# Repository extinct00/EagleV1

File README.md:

# EagleV1

## Low-cost split column-staggered ergonomic keyboard
A Corne-like split keyboard with a little bit wider thumb-cluster and more agressive pinky stagger. This keyboard is designed to be compatible with RedDragon LowProfile switches that are widely avaialable on AliExpress for very cheap. They have the same height as
Khail LP switches (around 12mm) and can be used with classic MX style keycaps, although some might hit the upper housing. Preffered are any keycaps compatible with Numphy keyboards or any 3D printed, either FDM or SLA.

---

## Table of Contents
1. [Introduction](#introduction)
2. [Features](#features)
3. [Bill of Materials](#bill-of-materials)
4. [Build Instructions](#build-instructions)
5. [Pictures](#pictures)
6. [Contributing](#contributing)
7. [License](#license)

---

## Introduction
This project is designed to create a split ergonomic keyboard that is both low-cost and low-profile. The keyboard is split into two halves, allowing for a more natural hand position and reducing strain during long typing sessions. The low-profile design ensures a sleek and modern look while maintaining comfort.

---

## Features
- **Split Design**: Ergonomically designed to reduce strain on your hands and wrists.
- **Low-Cost**: Built with affordable components to keep the project accessible.
- **Low-Profile**: Sleek and compact design for a modern look.
- **Customizable**: Open-source firmware and hardware for easy customization.

---

## Bill of Materials
Here’s a list of components you’ll need to build this keyboard. (You can fill this section with the specific parts you used.)

1. **Microcontroller**: (e.g., Pro Micro, RP2040, etc.)
2. **Key Switches**: (e.g., Low-profile mechanical switches)
3. **Keycaps**: (e.g., Low-profile keycaps)
4. **PCB or Handwiring Materials**: (e.g., PCB, diodes, wires)
5. **Case**: (e.g., 3D-printed or acrylic case)
6. **Connectors**: (e.g., TRRS cable for split communication)
7. **Miscellaneous**: (e.g., screws, standoffs, etc.)

---

## Build Instructions
Below is a step-by-step guide to building your split ergonomic keyboard. (You can fill in the details as you progress.)

### Step 1: Gather All Components
Ensure you have all the components listed in the [Bill of Materials](#bill-of-materials) section.

### Step 2: Prepare the PCB or Handwiring
- If using a PCB, solder the diodes and microcontroller.
- If handwiring, follow the wiring diagram and connect the switches to the microcontroller.

### Step 3: Assemble the Case
- Attach the switches to the case.
- Secure the PCB or handwired assembly into the case.

### Step 4: Connect the Two Halves
- Use a TRRS cable to connect the two halves of the keyboard.
- Ensure the firmware supports split communication.

### Step 5: Flash the Firmware
- Download and flash the firmware to the microcontroller.
- Customize the keymap if needed.

### Step 6: Test the Keyboard
- Connect the keyboard to your computer and test all keys.
- Make adjustments as necessary.

---

## Pictures
Here are some pictures of my progress and the final build. (You can add images from the `Pictures` folder as you go.)

---

## Contributing
Contributions are welcome! If you have any suggestions, improvements, or bug fixes, feel free to open an issue or submit a pull request.

---

## License
This project is licensed under the [MIT License](LICENSE). Feel free to use, modify, and distribute it as you see fit.

---

Happy building! 🎛️

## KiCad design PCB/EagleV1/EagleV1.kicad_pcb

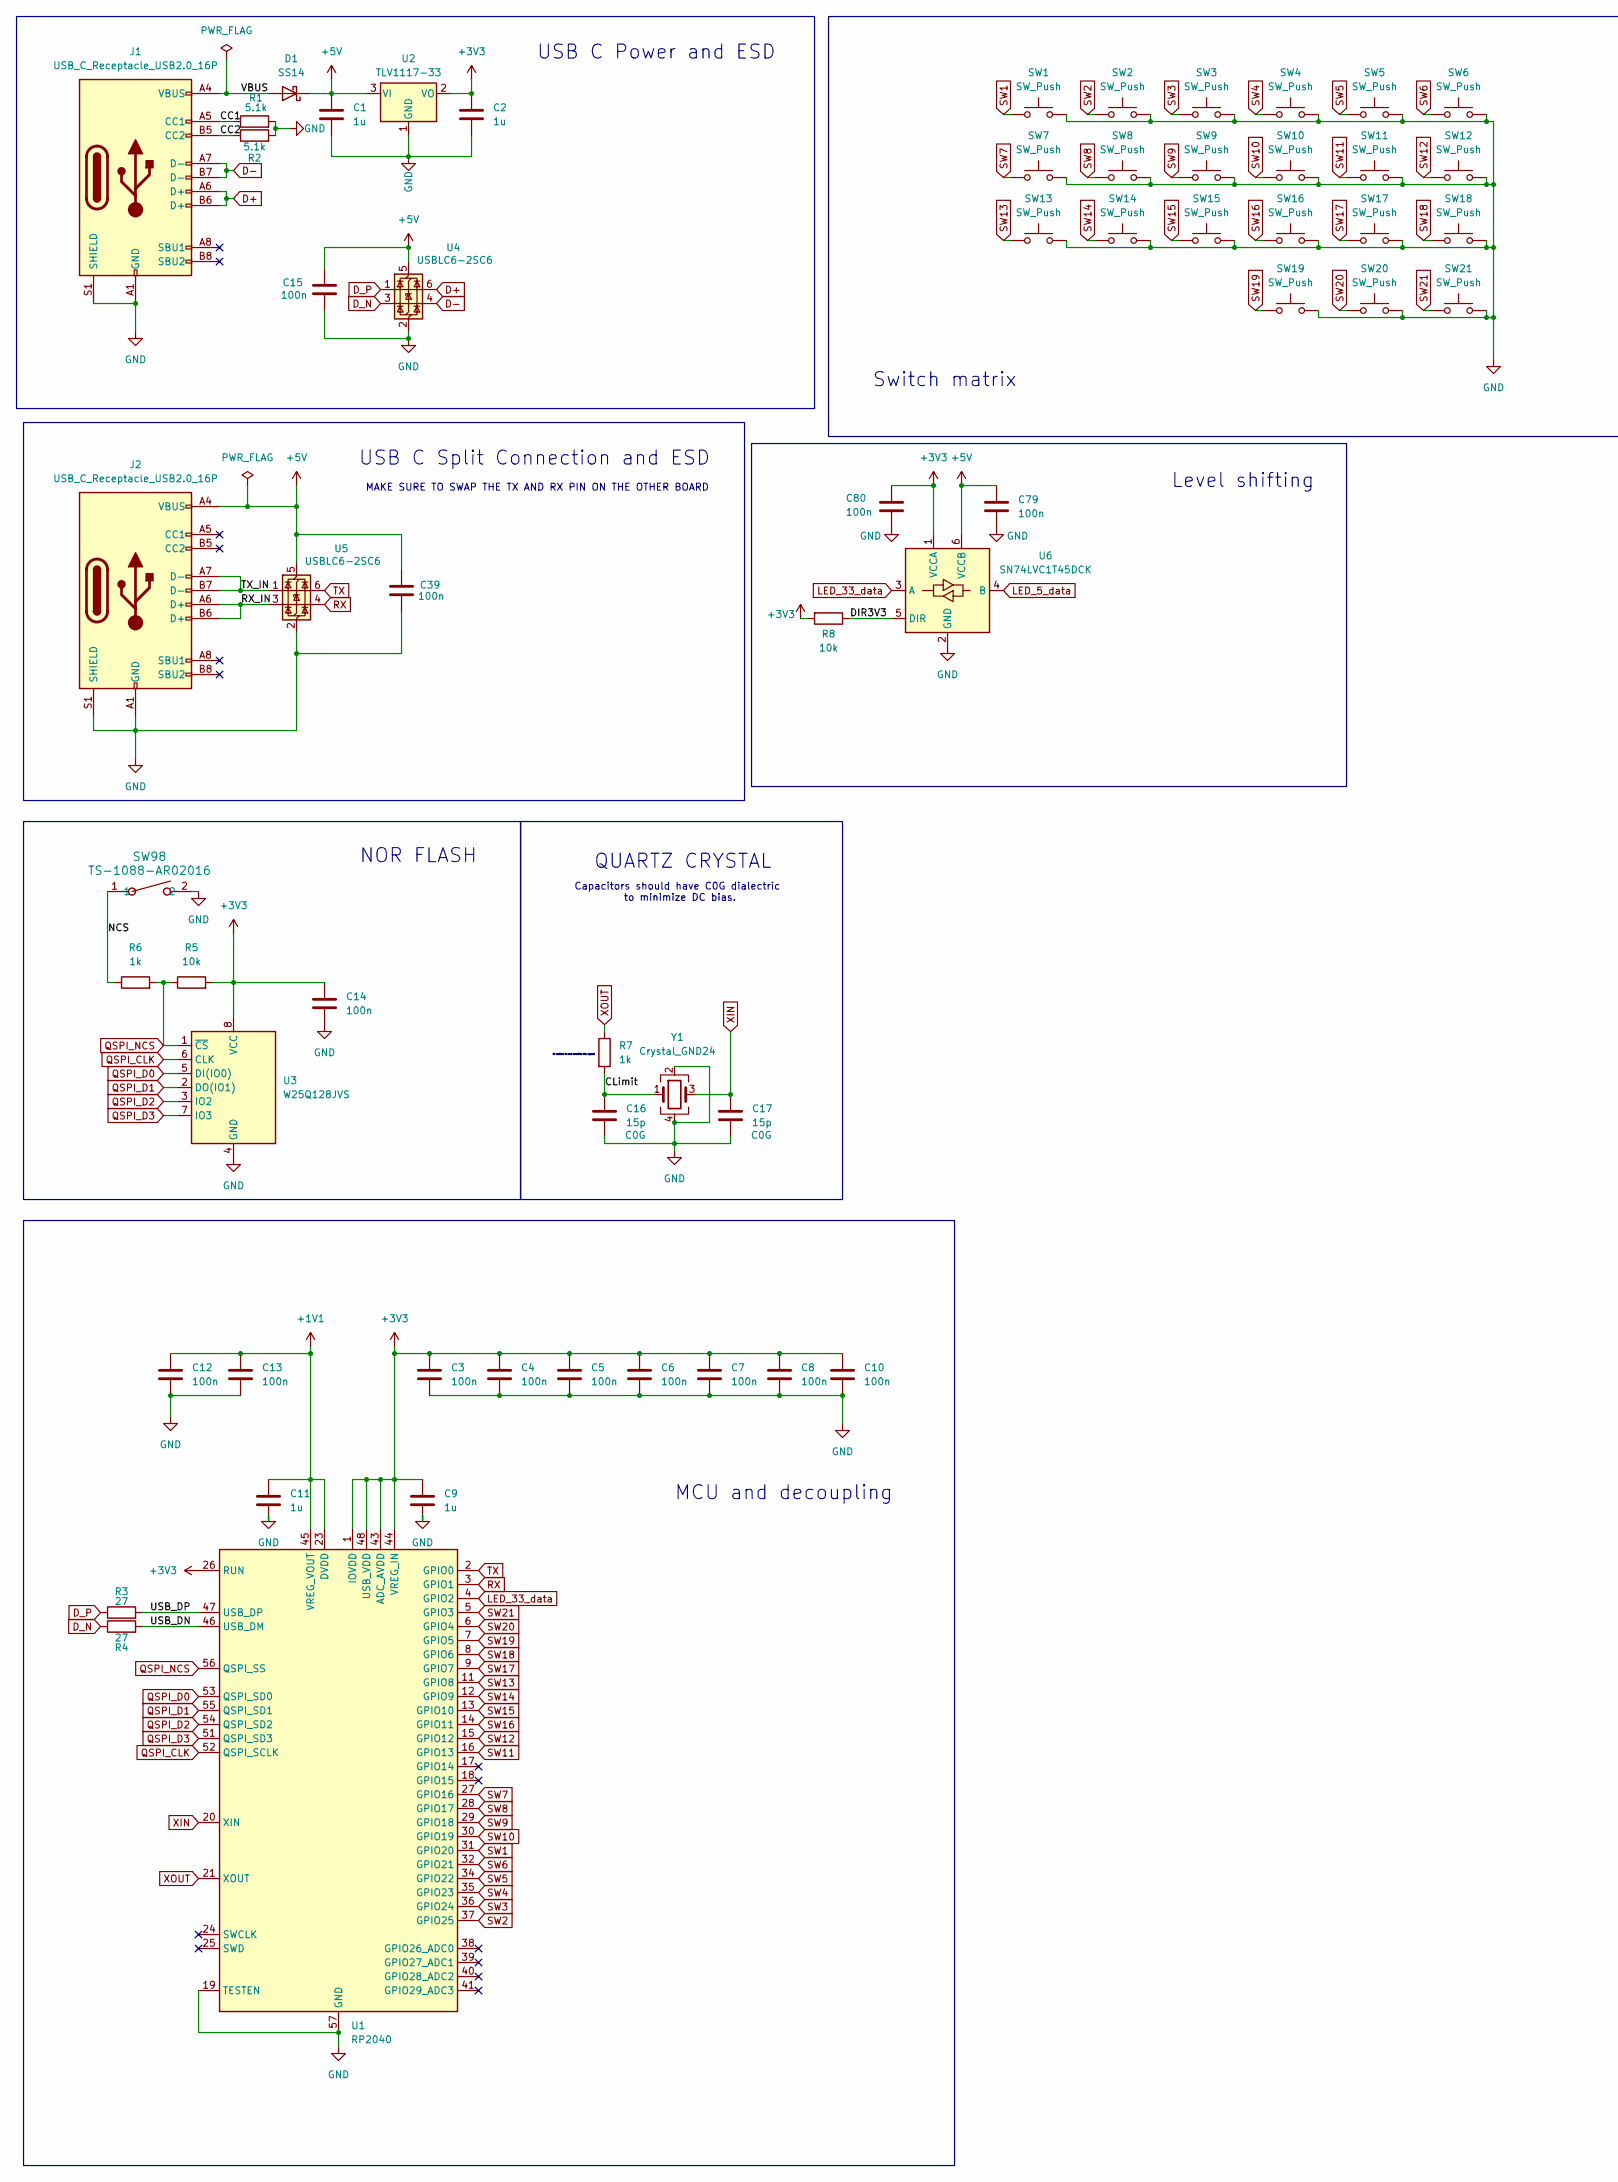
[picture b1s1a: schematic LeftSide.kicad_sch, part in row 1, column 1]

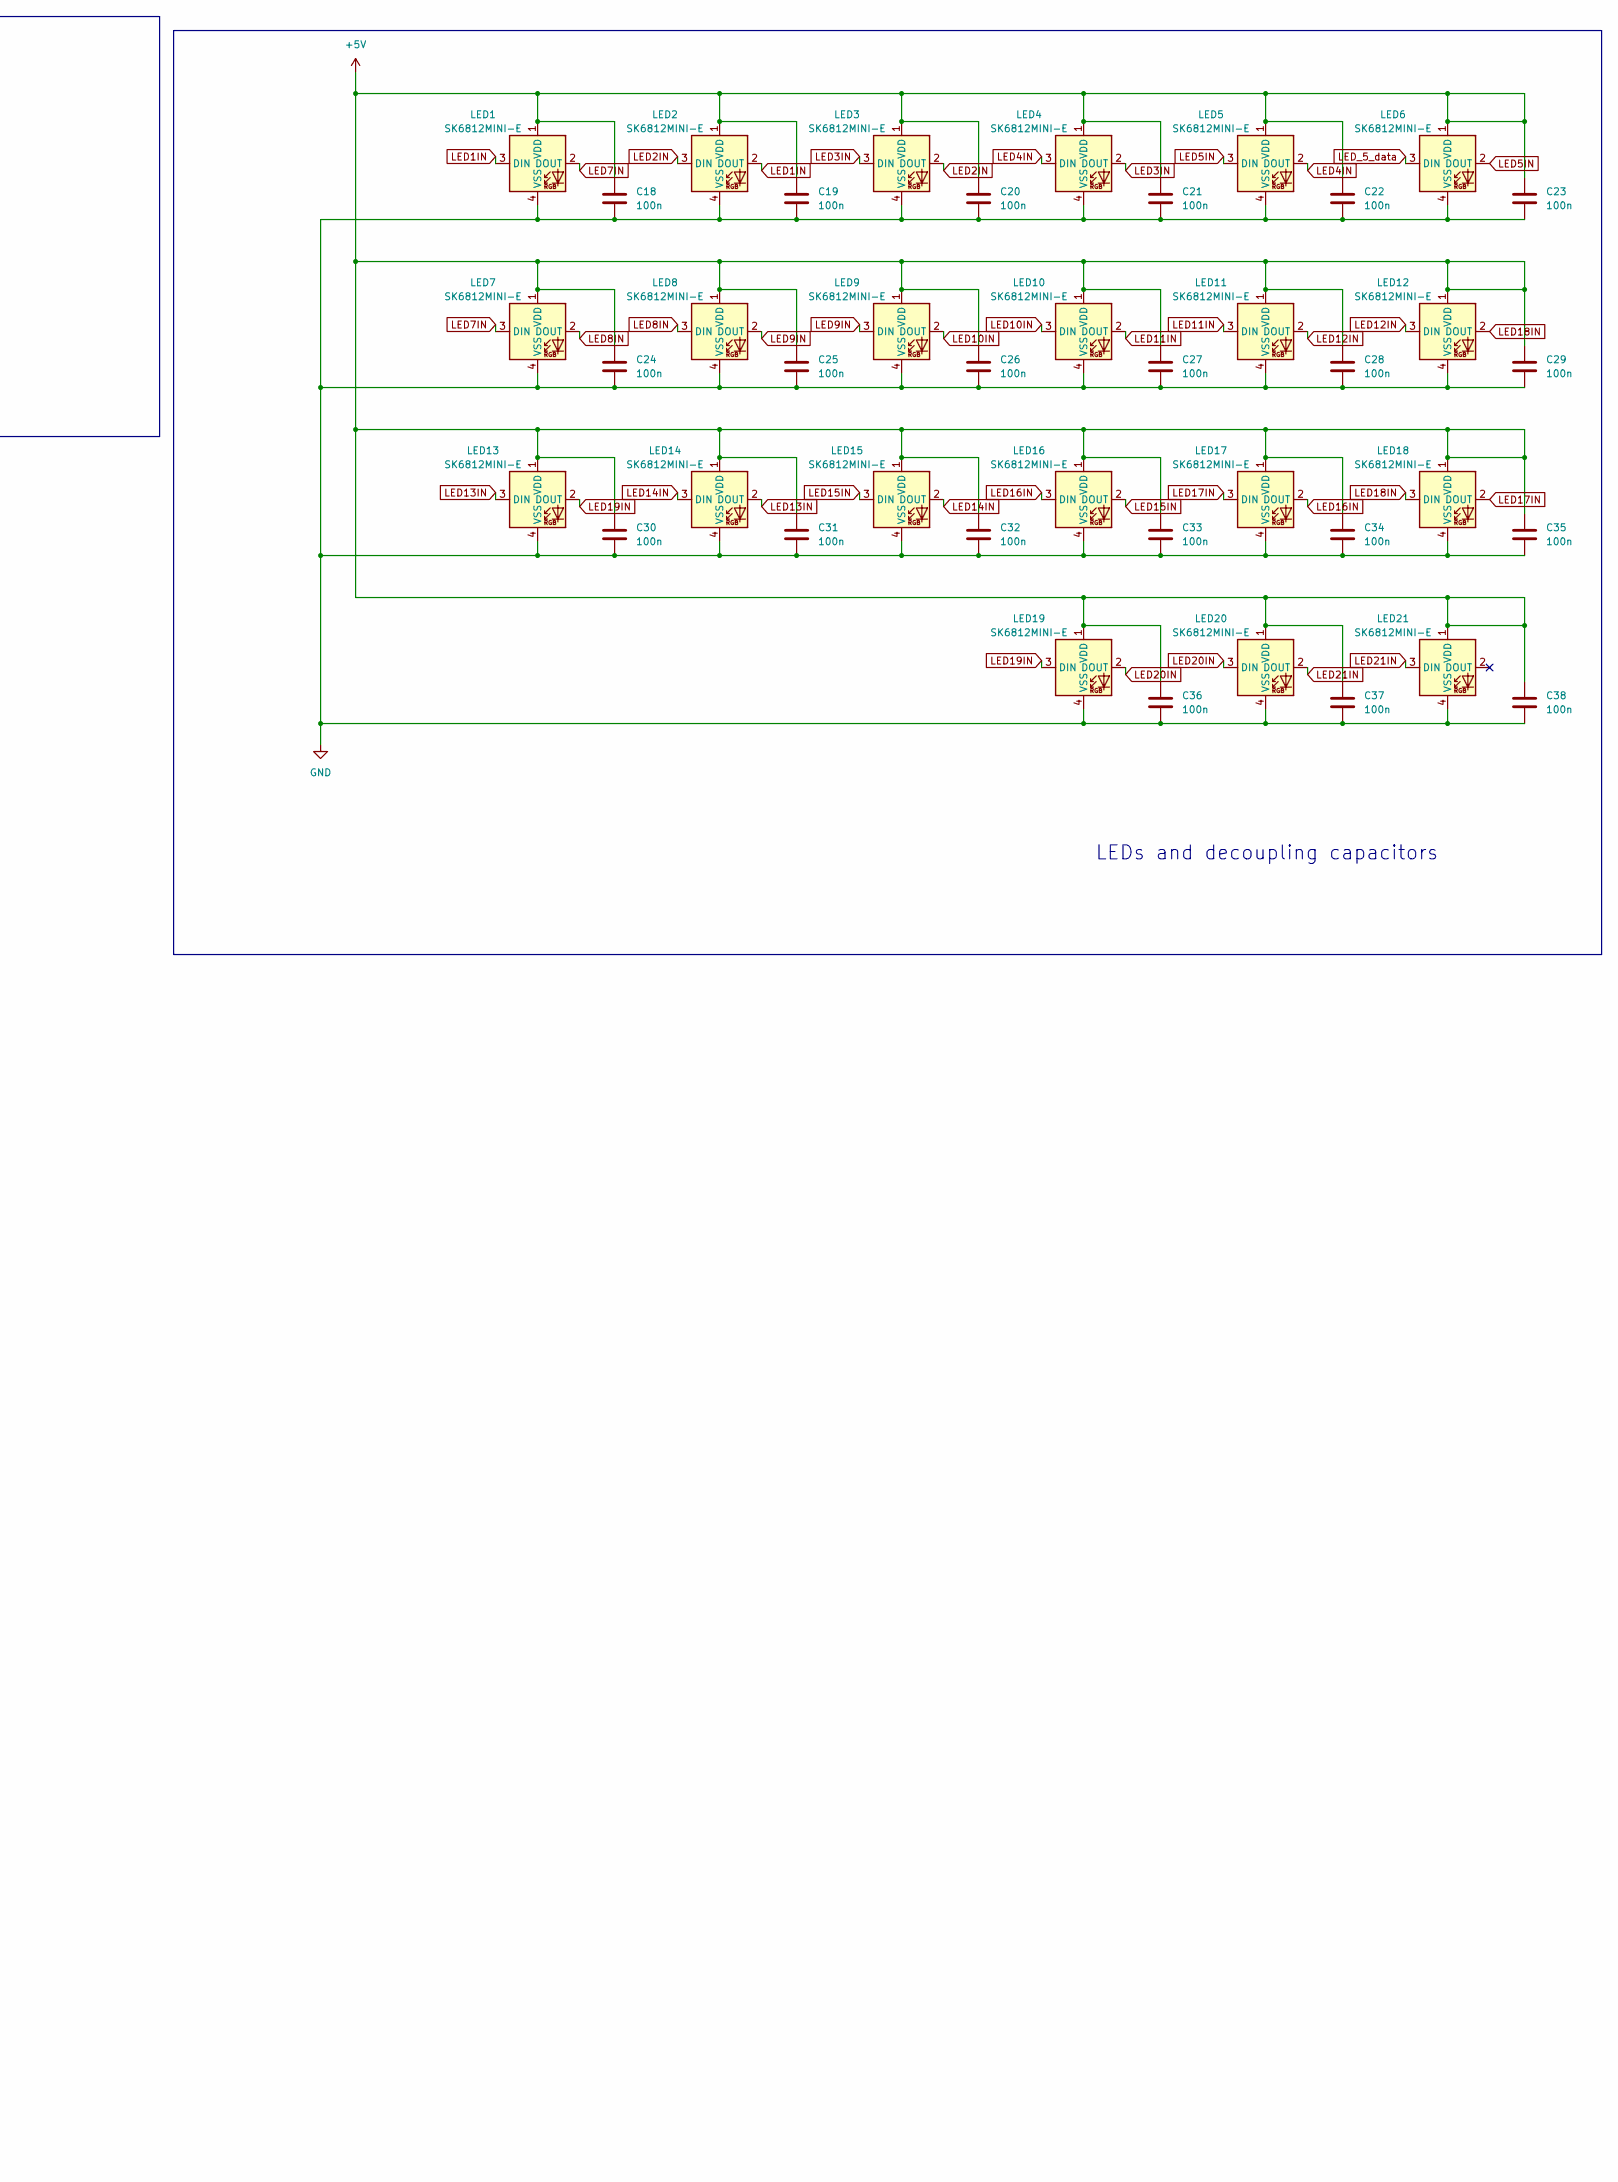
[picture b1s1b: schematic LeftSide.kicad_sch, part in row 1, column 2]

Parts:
C1, C2, C9, C11: 1u; C_0603_1608Metric
C3, C4, C5, C6, C7, C8, C10, C12, C13, C14, C15, C18, C19, C20, C21, C22, C23, C24, C25, C26, C27, C28, C29, C30, C31, C32, C33, C34, C35, C36, C37, C38, C39, C79, C80: 100n; C_0402_1005Metric
C16, C17: 15p; C_0402_1005Metric
D1: SS14; D_SMA
J1, J2: USB_C_Receptacle_USB2.0_16P; USB_C_Receptacle_G-Switch_GT-USB-7010ASV
LED1, LED2, LED3, LED4, LED5, LED6, LED7, LED8, LED9, LED10, LED11, LED12, LED13, LED14, LED15, LED16, LED17, LED18, LED19, LED20, LED21: SK6812MINI-E; LED_6028R
R1, R2: 5.1k; R_0402_1005Metric
R3, R4: 27; R_0402_1005Metric
R5, R8: 10k; R_0402_1005Metric
R6, R7: 1k; R_0402_1005Metric
SW1, SW2, SW3, SW4, SW5, SW6, SW7, SW8, SW9, SW10, SW11, SW12, SW13, SW14, SW15, SW16, SW17, SW18, SW19, SW20, SW21: SW_Push; SW_Redragon_LowProfile_PCB_1.00u
SW98: TS-1088-AR02016; SW_TS-1088_XNP
U1: RP2040; QFN-56-1EP_7x7mm_P0.4mm_EP3.2x3.2mm
U2: TLV1117-33; SOT-223-3_TabPin2
U3: W25Q128JVS; SOIC-8_5.23x5.23mm_P1.27mm
U4, U5: USBLC6-2SC6; SOT-23-6
U6: SN74LVC1T45DCK; SOT-363_SC-70-6
Y1: Crystal_GND24; Crystal_SMD_3225-4Pin_3.2x2.5mm

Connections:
+1V1: C11.1, C12.1, C13.1, U1.23 (DVDD), U1.45 (VREG_VOUT), U1.50 (DVDD)
+3V3: C2.1, C3.1, C4.1, C5.1, C6.1, C7.1, C8.1, C9.1, C10.1, C14.1, C80.1, R5.2, R8.2, U1.1 (IOVDD), U1.10 (IOVDD), U1.22 (IOVDD), U1.26 (RUN), U1.33 (IOVDD), U1.42 (IOVDD), U1.43 (ADC_AVDD), U1.44 (VREG_IN), U1.48 (USB_VDD), U1.49 (IOVDD), U2.2 (VO), U3.8 (VCC), U6.1 (VCCA)
+5V: C1.1, C15.2, C18.2, C19.2, C20.2, C21.2, C22.2, C23.2, C24.2, C25.2, C26.2, C27.2, C28.2, C29.2, C30.2, C31.2, C32.2, C33.2, C34.2, C35.2, C36.2, C37.2, C38.2, C39.2, C79.1, D1.1 (K), J2.A4 (VBUS), J2.A9 (VBUS), J2.B4 (VBUS), J2.B9 (VBUS), LED1.1 (VDD), LED2.1 (VDD), LED3.1 (VDD), LED4.1 (VDD), LED5.1 (VDD), LED6.1 (VDD), LED7.1 (VDD), LED8.1 (VDD), LED9.1 (VDD), LED10.1 (VDD), LED11.1 (VDD), LED12.1 (VDD), LED13.1 (VDD), LED14.1 (VDD), LED15.1 (VDD), LED16.1 (VDD), LED17.1 (VDD), LED18.1 (VDD), LED19.1 (VDD), LED20.1 (VDD), LED21.1 (VDD), U2.3 (VI), U4.5 (VBUS), U5.5 (VBUS), U6.6 (VCCB)
/LeftSide/CC1: J1.A5 (CC1), R1.1
/LeftSide/CC2: J1.B5 (CC2), R2.1
/LeftSide/CLimit: C16.1, R7.2, Y1.1
/LeftSide/DIR3V3: R8.1, U6.5 (DIR)
/LeftSide/NCS: R6.1, SW98.1
/LeftSide/RX_IN: J2.A6 (D+), J2.B6 (D+), U5.3 (I/O2)
/LeftSide/TX_IN: J2.A7 (D-), J2.B7 (D-), U5.1 (I/O1)
/LeftSide/USB_DN: R4.2, U1.46 (USB_DM)
/LeftSide/USB_DP: R3.2, U1.47 (USB_DP)
/LeftSide/VBUS: D1.2 (A), J1.A4 (VBUS), J1.A9 (VBUS), J1.B4 (VBUS), J1.B9 (VBUS)
D+: J1.A6 (D+), J1.B6 (D+), U4.6 (I/O1)
D-: J1.A7 (D-), J1.B7 (D-), U4.4 (I/O2)
D_N: R4.1, U4.3 (I/O2)
D_P: R3.1, U4.1 (I/O1)
GND: C1.2, C2.2, C3.2, C4.2, C5.2, C6.2, C7.2, C8.2, C9.2, C10.2, C11.2, C12.2, C13.2, C14.2, C15.1, C16.2, C17.2, C18.1, C19.1, C20.1, C21.1, C22.1, C23.1, C24.1, C25.1, C26.1, C27.1, C28.1, C29.1, C30.1, C31.1, C32.1, C33.1, C34.1, C35.1, C36.1, C37.1, C38.1, C39.1, C79.2, C80.2, J1.A1 (GND), J1.A12 (GND), J1.B1 (GND), J1.B12 (GND), J1.S1 (SHIELD), J2.A1 (GND), J2.A12 (GND), J2.B1 (GND), J2.B12 (GND), J2.S1 (SHIELD), LED1.4 (VSS), LED2.4 (VSS), LED3.4 (VSS), LED4.4 (VSS), LED5.4 (VSS), LED6.4 (VSS), LED7.4 (VSS), LED8.4 (VSS), LED9.4 (VSS), LED10.4 (VSS), LED11.4 (VSS), LED12.4 (VSS), LED13.4 (VSS), LED14.4 (VSS), LED15.4 (VSS), LED16.4 (VSS), LED17.4 (VSS), LED18.4 (VSS), LED19.4 (VSS), LED20.4 (VSS), LED21.4 (VSS), R1.2, R2.2, SW1.2, SW2.2, SW3.2, SW4.2, SW5.2, SW6.2, SW7.2, SW8.2, SW9.2, SW10.2, SW11.2, SW12.2, SW13.2, SW14.2, SW15.2, SW16.2, SW17.2, SW18.2, SW19.2, SW20.2, SW21.2, SW98.2, U1.19 (TESTEN), U1.57 (GND), U2.1 (GND), U3.4 (GND), U4.2 (GND), U5.2 (GND), U6.2 (GND), Y1.2, Y1.4
LED1IN: LED1.3 (DIN), LED2.2 (DOUT)
LED2IN: LED2.3 (DIN), LED3.2 (DOUT)
LED3IN: LED3.3 (DIN), LED4.2 (DOUT)
LED4IN: LED4.3 (DIN), LED5.2 (DOUT)
LED5IN: LED5.3 (DIN), LED6.2 (DOUT)
LED7IN: LED1.2 (DOUT), LED7.3 (DIN)
LED8IN: LED7.2 (DOUT), LED8.3 (DIN)
LED9IN: LED8.2 (DOUT), LED9.3 (DIN)
LED10IN: LED9.2 (DOUT), LED10.3 (DIN)
LED11IN: LED10.2 (DOUT), LED11.3 (DIN)
LED12IN: LED11.2 (DOUT), LED12.3 (DIN)
LED13IN: LED13.3 (DIN), LED14.2 (DOUT)
LED14IN: LED14.3 (DIN), LED15.2 (DOUT)
LED15IN: LED15.3 (DIN), LED16.2 (DOUT)
LED16IN: LED16.3 (DIN), LED17.2 (DOUT)
LED17IN: LED17.3 (DIN), LED18.2 (DOUT)
LED18IN: LED12.2 (DOUT), LED18.3 (DIN)
LED19IN: LED13.2 (DOUT), LED19.3 (DIN)
LED20IN: LED19.2 (DOUT), LED20.3 (DIN)
LED21IN: LED20.2 (DOUT), LED21.3 (DIN)
LED_5_data: LED6.3 (DIN), U6.4 (B)
LED_33_data: U1.4 (GPIO2), U6.3 (A)
QSPI_CLK: U1.52 (QSPI_SCLK), U3.6 (CLK)
QSPI_D0: U1.53 (QSPI_SD0), U3.5 (DI(IO0))
QSPI_D1: U1.55 (QSPI_SD1), U3.2 (DO(IO1))
QSPI_D2: U1.54 (QSPI_SD2), U3.3 (IO2)
QSPI_D3: U1.51 (QSPI_SD3), U3.7 (IO3)
QSPI_NCS: R5.1, R6.2, U1.56 (QSPI_SS), U3.1 (~CS)
RX: U1.3 (GPIO1), U5.4 (I/O2)
SW1: SW1.1, U1.31 (GPIO20)
SW2: SW2.1, U1.37 (GPIO25)
SW3: SW3.1, U1.36 (GPIO24)
SW4: SW4.1, U1.35 (GPIO23)
SW5: SW5.1, U1.34 (GPIO22)
SW6: SW6.1, U1.32 (GPIO21)
SW7: SW7.1, U1.27 (GPIO16)
SW8: SW8.1, U1.28 (GPIO17)
SW9: SW9.1, U1.29 (GPIO18)
SW10: SW10.1, U1.30 (GPIO19)
SW11: SW11.1, U1.16 (GPIO13)
SW12: SW12.1, U1.15 (GPIO12)
SW13: SW13.1, U1.11 (GPIO8)
SW14: SW14.1, U1.12 (GPIO9)
SW15: SW15.1, U1.13 (GPIO10)
SW16: SW16.1, U1.14 (GPIO11)
SW17: SW17.1, U1.9 (GPIO7)
SW18: SW18.1, U1.8 (GPIO6)
SW19: SW19.1, U1.7 (GPIO5)
SW20: SW20.1, U1.6 (GPIO4)
SW21: SW21.1, U1.5 (GPIO3)
TX: U1.2 (GPIO0), U5.6 (I/O1)
XIN: C17.1, U1.20 (XIN), Y1.3
XOUT: R7.1, U1.21 (XOUT)

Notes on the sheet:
Capacitors should have C0G dialectric to minimize DC bias.
NOR FLASH
MAKE SURE TO SWAP THE TX AND RX PIN ON THE OTHER BOARD
USB C Power and ESD
LEDs and decoupling capacitors
1k resistor to not overdrive the crystal
USB C Split Connection and ESD
Level shifting
MCU and decoupling
QUARTZ CRYSTAL
Switch matrix

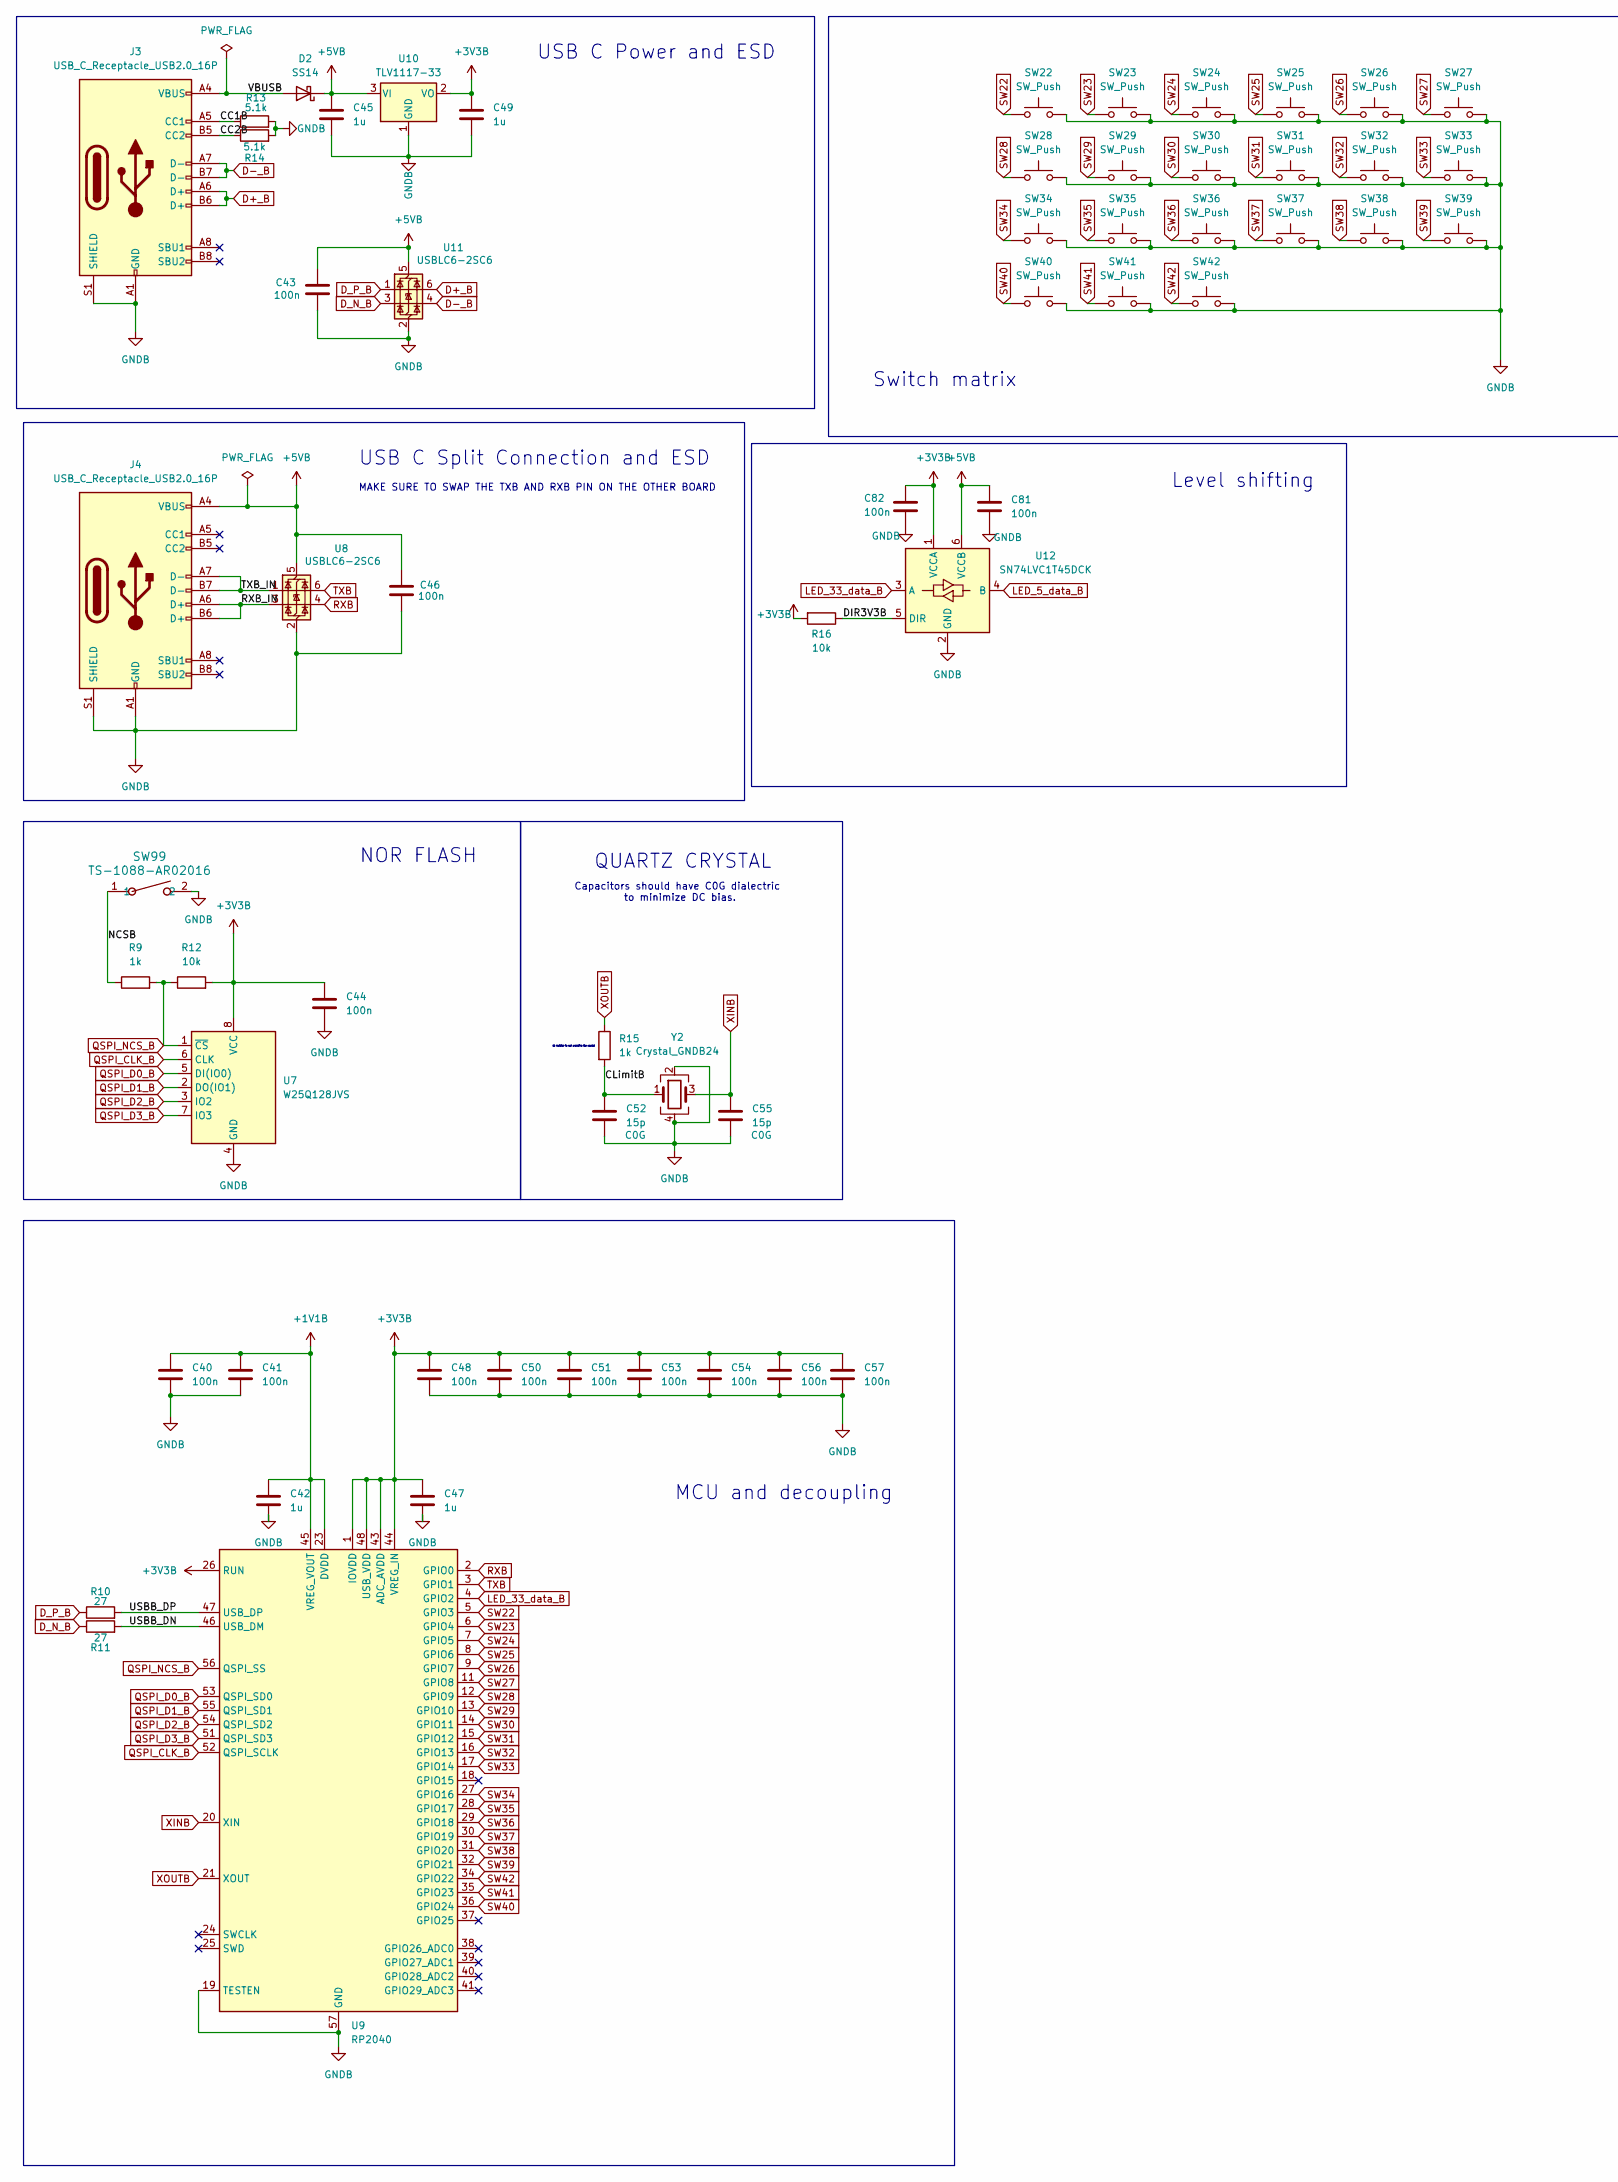
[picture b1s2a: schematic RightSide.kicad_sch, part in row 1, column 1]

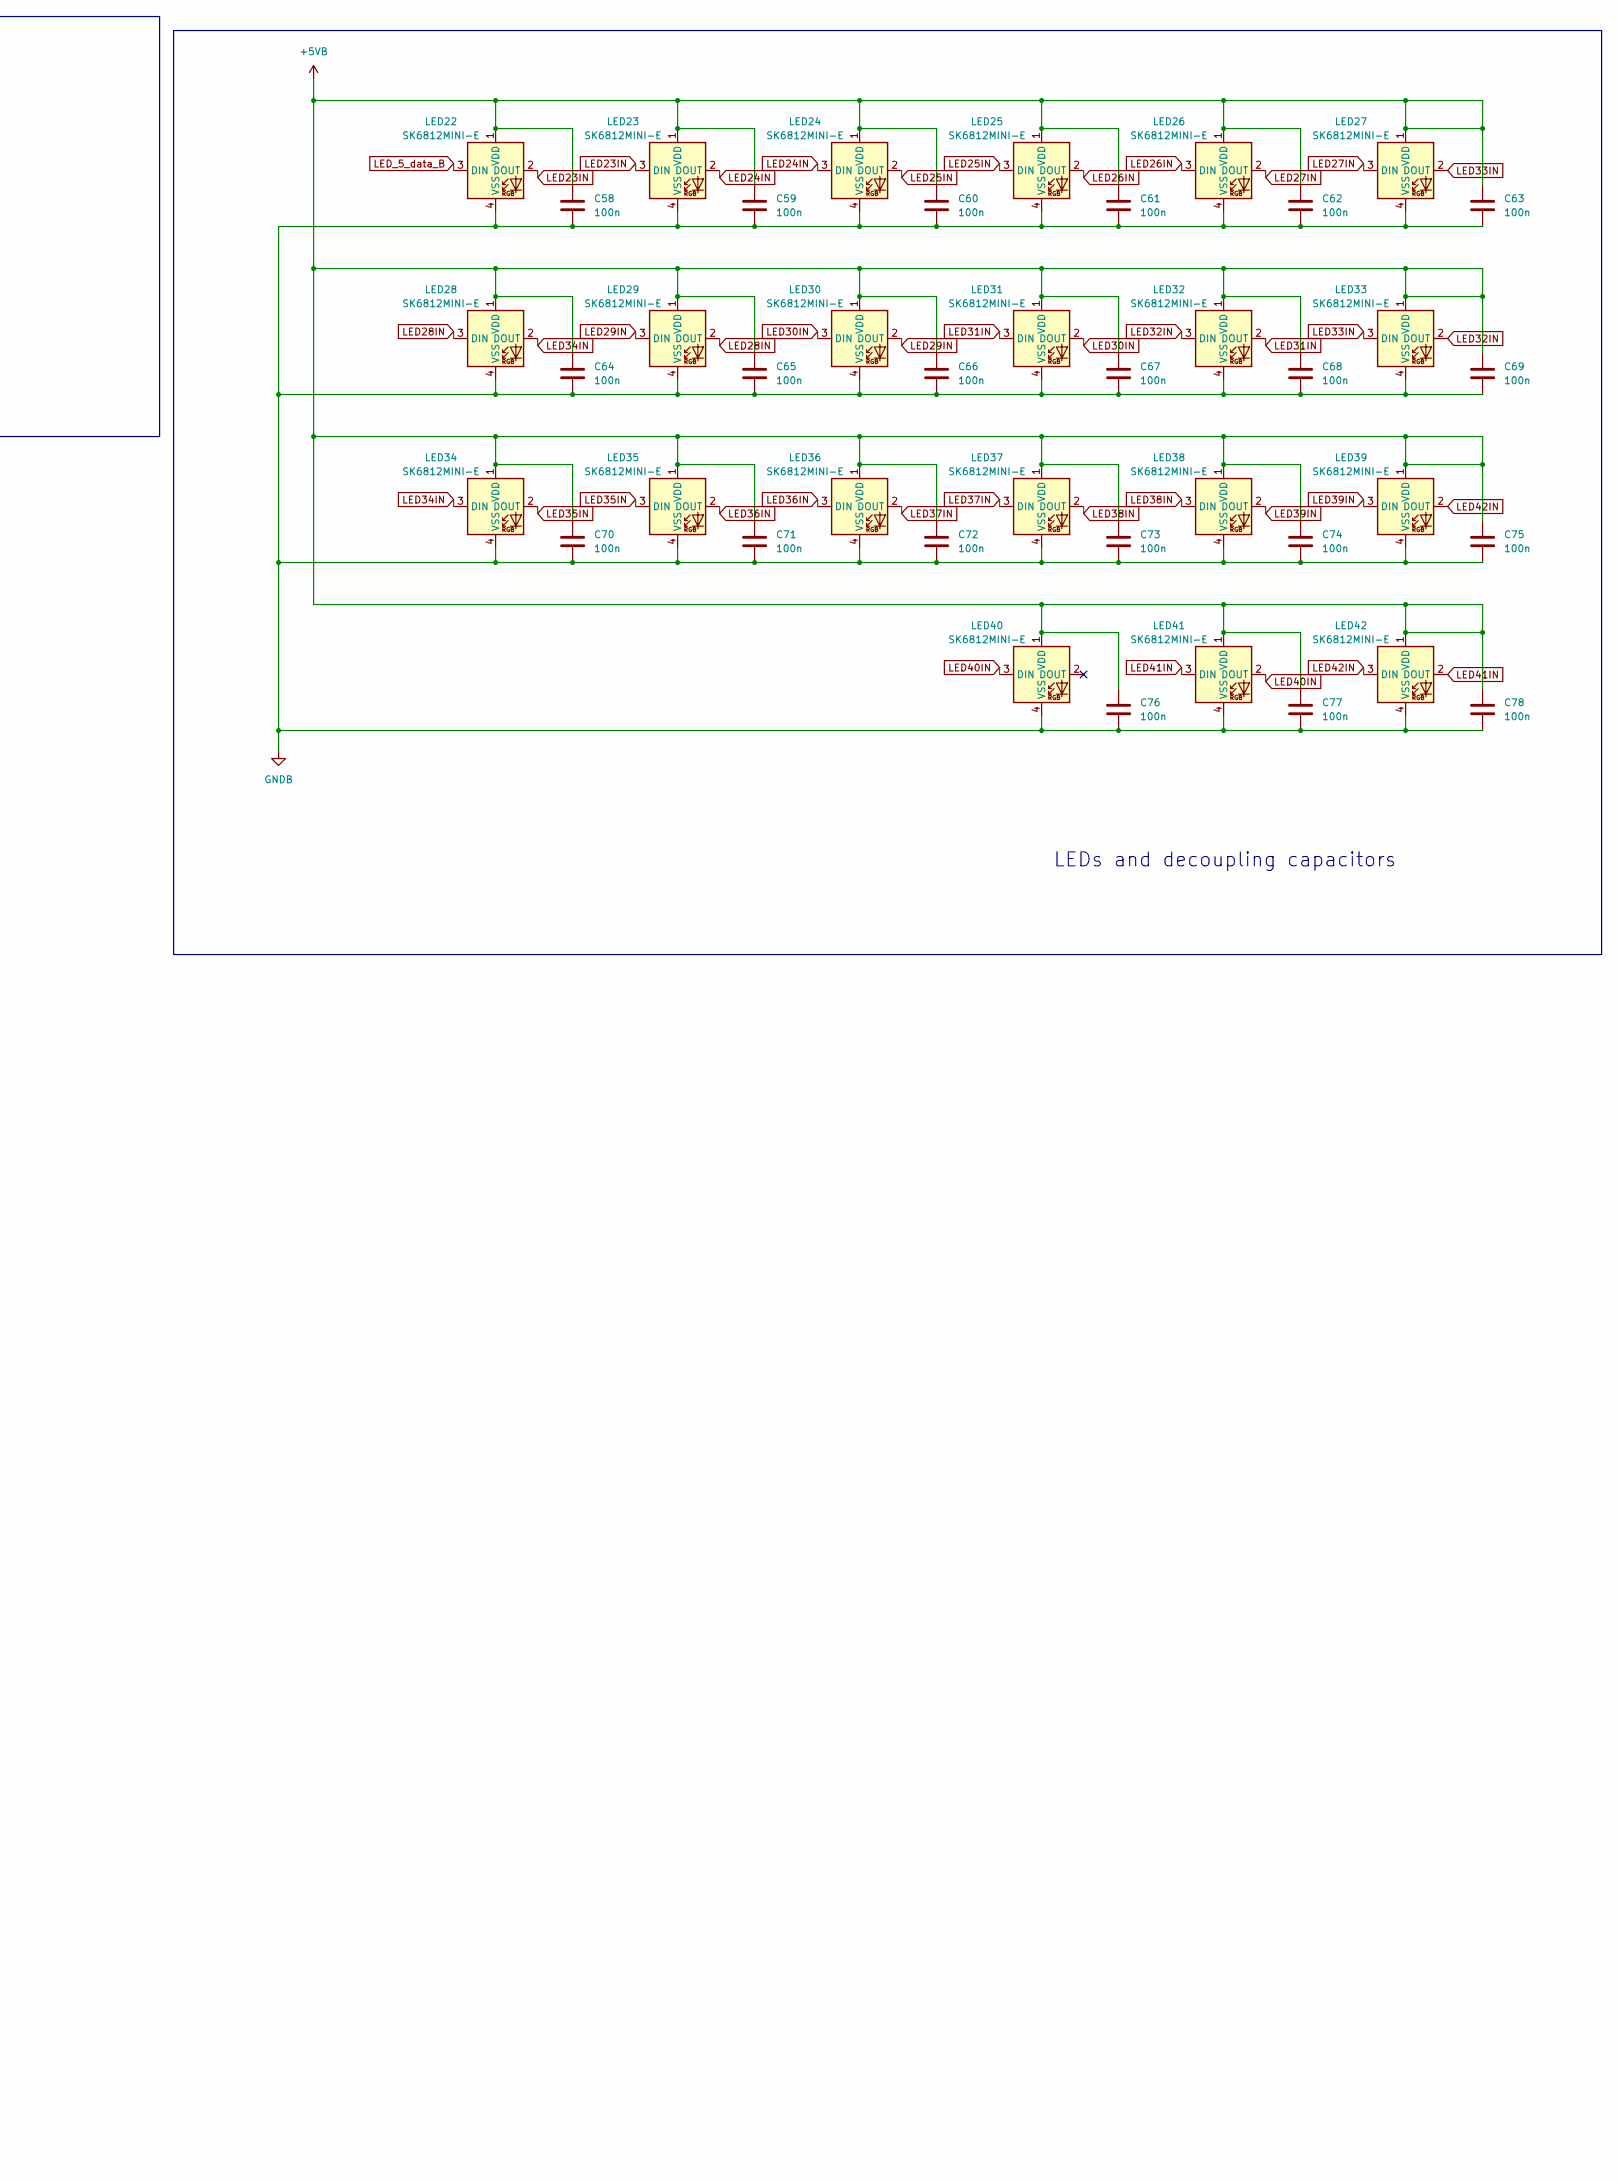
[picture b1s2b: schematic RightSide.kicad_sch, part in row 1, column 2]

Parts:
C40, C41, C43, C44, C46, C48, C50, C51, C53, C54, C56, C57, C58, C59, C60, C61, C62, C63, C64, C65, C66, C67, C68, C69, C70, C71, C72, C73, C74, C75, C76, C77, C78, C81, C82: 100n; C_0402_1005Metric
C42, C45, C47, C49: 1u; C_0603_1608Metric
C52, C55: 15p; C_0402_1005Metric
D2: SS14; D_SMA
J3, J4: USB_C_Receptacle_USB2.0_16P; USB_C_Receptacle_G-Switch_GT-USB-7010ASV
LED22, LED23, LED24, LED25, LED26, LED27, LED28, LED29, LED30, LED31, LED32, LED33, LED34, LED35, LED36, LED37, LED38, LED39, LED40, LED41, LED42: SK6812MINI-E; LED_6028R
R9, R15: 1k; R_0402_1005Metric
R10, R11: 27; R_0402_1005Metric
R12, R16: 10k; R_0402_1005Metric
R13, R14: 5.1k; R_0402_1005Metric
SW22, SW23, SW24, SW25, SW26, SW27, SW28, SW29, SW30, SW31, SW32, SW33, SW34, SW35, SW36, SW37, SW38, SW39, SW40, SW41, SW42: SW_Push; SW_Redragon_LowProfile_PCB_1.00u
SW99: TS-1088-AR02016; SW_TS-1088_XNP
U7: W25Q128JVS; SOIC-8_5.23x5.23mm_P1.27mm
U8, U11: USBLC6-2SC6; SOT-23-6
U9: RP2040; QFN-56-1EP_7x7mm_P0.4mm_EP3.2x3.2mm
U10: TLV1117-33; SOT-223-3_TabPin2
U12: SN74LVC1T45DCK; SOT-363_SC-70-6
Y2: Crystal_GNDB24; Crystal_SMD_3225-4Pin_3.2x2.5mm

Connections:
+1V1B: C40.1, C41.1, C42.1, U9.23 (DVDD), U9.45 (VREG_VOUT), U9.50 (DVDD)
+3V3B: C44.1, C47.1, C48.1, C49.1, C50.1, C51.1, C53.1, C54.1, C56.1, C57.1, C82.1, R12.2, R16.2, U7.8 (VCC), U9.1 (IOVDD), U9.10 (IOVDD), U9.22 (IOVDD), U9.26 (RUN), U9.33 (IOVDD), U9.42 (IOVDD), U9.43 (ADC_AVDD), U9.44 (VREG_IN), U9.48 (USB_VDD), U9.49 (IOVDD), U10.2 (VO), U12.1 (VCCA)
+5VB: C43.2, C45.1, C46.2, C58.2, C59.2, C60.2, C61.2, C62.2, C63.2, C64.2, C65.2, C66.2, C67.2, C68.2, C69.2, C70.2, C71.2, C72.2, C73.2, C74.2, C75.2, C76.2, C77.2, C78.2, C81.1, D2.1 (K), J4.A4 (VBUS), J4.A9 (VBUS), J4.B4 (VBUS), J4.B9 (VBUS), LED22.1 (VDD), LED23.1 (VDD), LED24.1 (VDD), LED25.1 (VDD), LED26.1 (VDD), LED27.1 (VDD), LED28.1 (VDD), LED29.1 (VDD), LED30.1 (VDD), LED31.1 (VDD), LED32.1 (VDD), LED33.1 (VDD), LED34.1 (VDD), LED35.1 (VDD), LED36.1 (VDD), LED37.1 (VDD), LED38.1 (VDD), LED39.1 (VDD), LED40.1 (VDD), LED41.1 (VDD), LED42.1 (VDD), U8.5 (VBUS), U10.3 (VI), U11.5 (VBUS), U12.6 (VCCB)
/RightSide/CC1B: J3.A5 (CC1), R13.1
/RightSide/CC2B: J3.B5 (CC2), R14.1
/RightSide/CLimitB: C52.1, R15.2, Y2.1
/RightSide/DIR3V3B: R16.1, U12.5 (DIR)
/RightSide/NCSB: R9.1, SW99.1
/RightSide/RXB_IN: J4.A6 (D+), J4.B6 (D+), U8.3 (I/O2)
/RightSide/TXB_IN: J4.A7 (D-), J4.B7 (D-), U8.1 (I/O1)
/RightSide/USBB_DN: R11.2, U9.46 (USB_DM)
/RightSide/USBB_DP: R10.2, U9.47 (USB_DP)
/RightSide/VBUSB: D2.2 (A), J3.A4 (VBUS), J3.A9 (VBUS), J3.B4 (VBUS), J3.B9 (VBUS)
D+_B: J3.A6 (D+), J3.B6 (D+), U11.6 (I/O1)
D-_B: J3.A7 (D-), J3.B7 (D-), U11.4 (I/O2)
D_N_B: R11.1, U11.3 (I/O2)
D_P_B: R10.1, U11.1 (I/O1)
GNDB: C40.2, C41.2, C42.2, C43.1, C44.2, C45.2, C46.1, C47.2, C48.2, C49.2, C50.2, C51.2, C52.2, C53.2, C54.2, C55.2, C56.2, C57.2, C58.1, C59.1, C60.1, C61.1, C62.1, C63.1, C64.1, C65.1, C66.1, C67.1, C68.1, C69.1, C70.1, C71.1, C72.1, C73.1, C74.1, C75.1, C76.1, C77.1, C78.1, C81.2, C82.2, J3.A1 (GND), J3.A12 (GND), J3.B1 (GND), J3.B12 (GND), J3.S1 (SHIELD), J4.A1 (GND), J4.A12 (GND), J4.B1 (GND), J4.B12 (GND), J4.S1 (SHIELD), LED22.4 (VSS), LED23.4 (VSS), LED24.4 (VSS), LED25.4 (VSS), LED26.4 (VSS), LED27.4 (VSS), LED28.4 (VSS), LED29.4 (VSS), LED30.4 (VSS), LED31.4 (VSS), LED32.4 (VSS), LED33.4 (VSS), LED34.4 (VSS), LED35.4 (VSS), LED36.4 (VSS), LED37.4 (VSS), LED38.4 (VSS), LED39.4 (VSS), LED40.4 (VSS), LED41.4 (VSS), LED42.4 (VSS), R13.2, R14.2, SW22.2, SW23.2, SW24.2, SW25.2, SW26.2, SW27.2, SW28.2, SW29.2, SW30.2, SW31.2, SW32.2, SW33.2, SW34.2, SW35.2, SW36.2, SW37.2, SW38.2, SW39.2, SW40.2, SW41.2, SW42.2, SW99.2, U7.4 (GND), U8.2 (GND), U9.19 (TESTEN), U9.57 (GND), U10.1 (GND), U11.2 (GND), U12.2 (GND), Y2.2, Y2.4
LED23IN: LED22.2 (DOUT), LED23.3 (DIN)
LED24IN: LED23.2 (DOUT), LED24.3 (DIN)
LED25IN: LED24.2 (DOUT), LED25.3 (DIN)
LED26IN: LED25.2 (DOUT), LED26.3 (DIN)
LED27IN: LED26.2 (DOUT), LED27.3 (DIN)
LED28IN: LED28.3 (DIN), LED29.2 (DOUT)
LED29IN: LED29.3 (DIN), LED30.2 (DOUT)
LED30IN: LED30.3 (DIN), LED31.2 (DOUT)
LED31IN: LED31.3 (DIN), LED32.2 (DOUT)
LED32IN: LED32.3 (DIN), LED33.2 (DOUT)
LED33IN: LED27.2 (DOUT), LED33.3 (DIN)
LED34IN: LED28.2 (DOUT), LED34.3 (DIN)
LED35IN: LED34.2 (DOUT), LED35.3 (DIN)
LED36IN: LED35.2 (DOUT), LED36.3 (DIN)
LED37IN: LED36.2 (DOUT), LED37.3 (DIN)
LED38IN: LED37.2 (DOUT), LED38.3 (DIN)
LED39IN: LED38.2 (DOUT), LED39.3 (DIN)
LED40IN: LED40.3 (DIN), LED41.2 (DOUT)
LED41IN: LED41.3 (DIN), LED42.2 (DOUT)
LED42IN: LED39.2 (DOUT), LED42.3 (DIN)
LED_5_data_B: LED22.3 (DIN), U12.4 (B)
LED_33_data_B: U9.4 (GPIO2), U12.3 (A)
QSPI_CLK_B: U7.6 (CLK), U9.52 (QSPI_SCLK)
QSPI_D0_B: U7.5 (DI(IO0)), U9.53 (QSPI_SD0)
QSPI_D1_B: U7.2 (DO(IO1)), U9.55 (QSPI_SD1)
QSPI_D2_B: U7.3 (IO2), U9.54 (QSPI_SD2)
QSPI_D3_B: U7.7 (IO3), U9.51 (QSPI_SD3)
QSPI_NCS_B: R9.2, R12.1, U7.1 (~CS), U9.56 (QSPI_SS)
RXB: U8.4 (I/O2), U9.2 (GPIO0)
SW22: SW22.1, U9.5 (GPIO3)
SW23: SW23.1, U9.6 (GPIO4)
SW24: SW24.1, U9.7 (GPIO5)
SW25: SW25.1, U9.8 (GPIO6)
SW26: SW26.1, U9.9 (GPIO7)
SW27: SW27.1, U9.11 (GPIO8)
SW28: SW28.1, U9.12 (GPIO9)
SW29: SW29.1, U9.13 (GPIO10)
SW30: SW30.1, U9.14 (GPIO11)
SW31: SW31.1, U9.15 (GPIO12)
SW32: SW32.1, U9.16 (GPIO13)
SW33: SW33.1, U9.17 (GPIO14)
SW34: SW34.1, U9.27 (GPIO16)
SW35: SW35.1, U9.28 (GPIO17)
SW36: SW36.1, U9.29 (GPIO18)
SW37: SW37.1, U9.30 (GPIO19)
SW38: SW38.1, U9.31 (GPIO20)
SW39: SW39.1, U9.32 (GPIO21)
SW40: SW40.1, U9.36 (GPIO24)
SW41: SW41.1, U9.35 (GPIO23)
SW42: SW42.1, U9.34 (GPIO22)
TXB: U8.6 (I/O1), U9.3 (GPIO1)
XINB: C55.1, U9.20 (XIN), Y2.3
XOUTB: R15.1, U9.21 (XOUT)

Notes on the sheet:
Capacitors should have C0G dialectric to minimize DC bias.
1k resistor to not overdrive the crystal
Level shifting
NOR FLASH
MCU and decoupling
USB C Split Connection and ESD
Switch matrix
QUARTZ CRYSTAL
LEDs and decoupling capacitors
USB C Power and ESD
MAKE SURE TO SWAP THE TXB AND RXB PIN ON THE OTHER BOARD
